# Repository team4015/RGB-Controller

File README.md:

# RGB Controller
Hardware and firmware for controlling LED RGB strips on FRC robots.

## Protocol

The RGB Controller circuit board contains a PIC16F690 microcontroller that sets the RGB colour using PWM signals.  The PIC runs the C firmware found in the `firmware` folder.  The RoboRIO can talk to the PIC using the following specific protocol:

By default, the PIC waits for the byte `0xFF` on its RX line.  Any other bytes will be discarded.  Once the PIC receives the `0xFF` header byte, it will receive three more bytes from the RX line.  These three bytes are used as the RGB brightness values.  Therefore, so set the RGB colour, the RoboRIO must send a total of 4 bytes:

```python
header = 0xFF

# RGB values must be between 0 and 255
red = 128
green = 255
blue = 0

packet = [header, red, green, blue]
send(packet)
```

**NOTE:** The PIC will never respond to the RoboRIO by sending back data.  Lights are a non-critical feature of the robot so the RoboRIO should not sit around waiting for the PIC to respond.

# Serial Port

The PIC communicates with the RoboRIO over UART, using only the TX and RX lines.  You will also need to connect the GND lines between the RGB controller board and the serial port on the RoboRIO.  The baud rate must be `9600` bps (the exact baud rate is `9615` if you want to be super precise).  No parity bits are used.  The size of one byte must be 8 bits.

**IMPORTANT:**  The PIC cannot receive more than one byte at a time.  Therefore, make sure that the RoboRIO sends data one byte at a time, with a delay of 1.5 ms between each byte.  It is advised to flush the serial port TX buffer after writing each byte.  See the Python script `rgb.py` under `firmware` for an example.

# Python Test Scripts

There are two Python test scripts: `rgb.py` and `rainbow.py`.  `rgb.py` is used to set a specific RGB colour once.  `rainbow.py` will run through the colour spectrum.

First install `pyserial`:
```
pip3 install pyserial
```

To run `rgb.py`:
```
python3 rgb.py <red> <green> <blue>
```
`red`, `green`, and `blue` must be values from `0` to `255`.

To run `rainbow.py`:
```
python3 rainbow.py
```

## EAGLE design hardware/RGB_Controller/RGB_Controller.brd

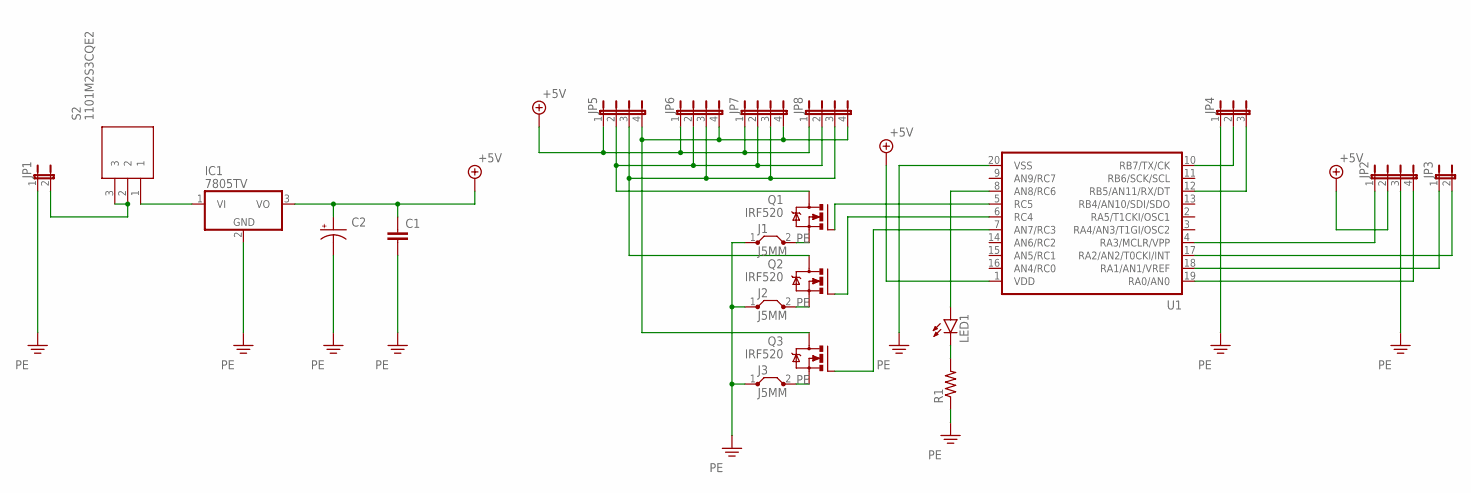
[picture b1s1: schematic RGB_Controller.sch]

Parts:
C1: C-EU025-024X044; C025-024X044
C2: CPOL-USE3.5-10; E3,5-10
IC1: 7805TV; TO220V
J1, J2, J3: J5MM; 05
JP1, JP3: JP1E; JP1
JP2, JP5, JP6, JP7, JP8: JP4E; JP4
JP4: JP2E; JP2
LED1: LED5MM
Q1, Q2, Q3: IRF520; TO220BV
R1: R-US_0207/10; 0207/10
S2: 1101M2S3CQE2; 1000-SERIES(SPDT)
U1: PIC16F6XX; DIL20

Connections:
+5V: C1.1, C2.+, IC1.3 (VO), JP2.2, JP5.1, JP6.1, JP7.1, JP8.1, U1.1 (VDD)
unnamed: JP1.2, S2.2, S2.3
unnamed: JP2.1, U1.4 (RA3/MCLR/VPP)
unnamed: LED1.K (C), R1.2
unnamed: JP2.4, U1.19 (RA0/AN0)
unnamed: JP3.1, U1.18 (RA1/AN1/VREF)
unnamed: JP3.2, U1.17 (RA2/AN2/T0CKI/INT)
unnamed: JP4.2, U1.10 (RB7/TX/CK)
unnamed: JP4.3, U1.12 (RB5/AN11/RX/DT)
unnamed: Q1.G, U1.5 (RC5)
unnamed: Q2.G, U1.6 (RC4)
unnamed: Q3.G, U1.7 (AN7/RC3)
unnamed: JP5.2, JP6.2, JP7.2, JP8.2, Q1.D
unnamed: JP5.3, JP6.3, JP7.3, JP8.3, Q2.D
unnamed: JP5.4, JP6.4, JP7.4, JP8.4, Q3.D
unnamed: LED1.A, U1.8 (AN8/RC6)
unnamed: IC1.1 (VI), S2.1
PE: C1.2, C2.-, IC1.2 (GND), J1.1, J1.2, J2.1, J2.2, J3.1, J3.2, JP1.1, JP2.3, JP4.1, Q1.S, Q2.S, Q3.S, R1.1, U1.20 (VSS)

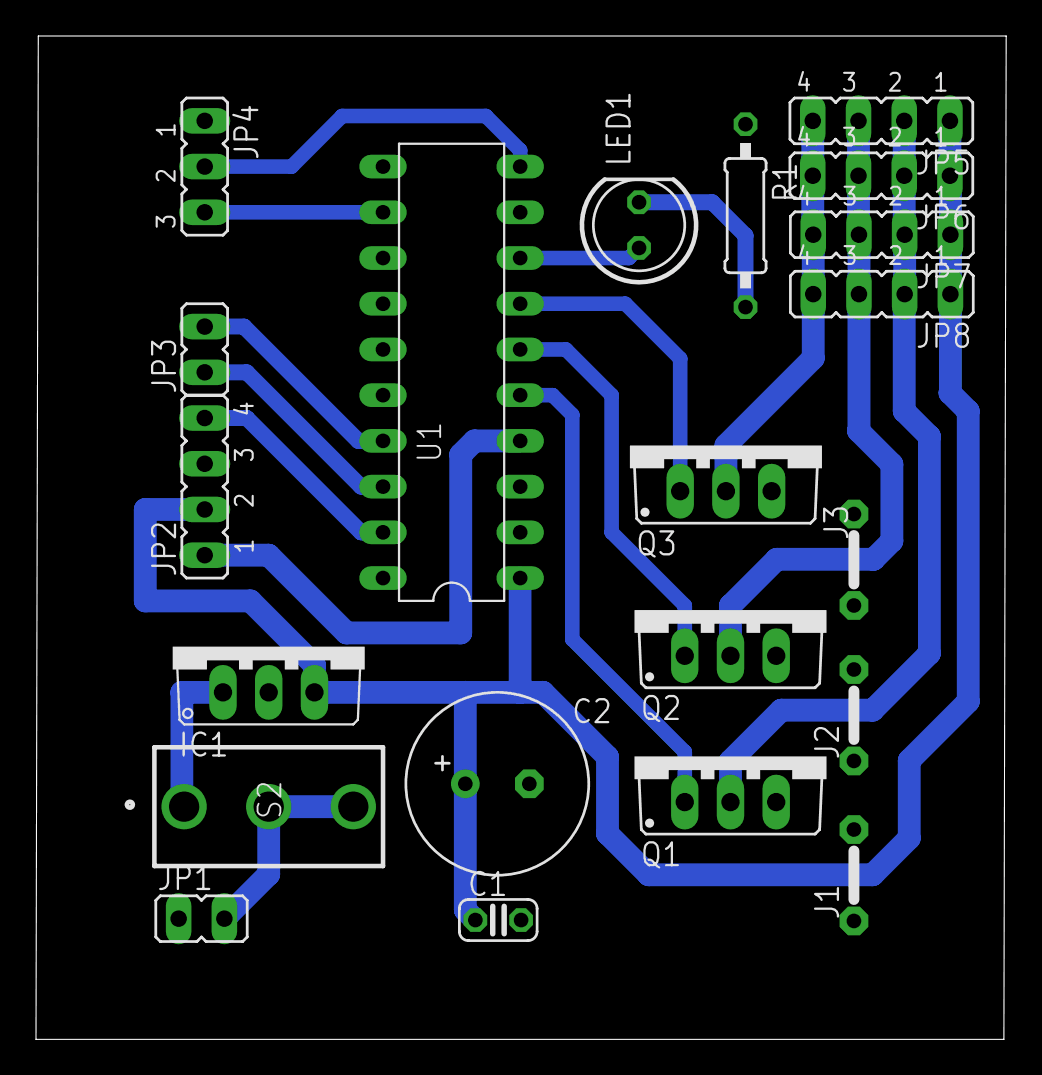
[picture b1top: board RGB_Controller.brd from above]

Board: 2 copper layers, 53.9 x 55.7 mm, 21 parts (0 on the bottom side), 18 nets.

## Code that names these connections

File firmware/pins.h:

#ifndef PINS_H
#define PINS_H

// STATUS LED //

#define LED        RC6
#define LED_TRIS   TRISC6

// RGB LEDS //

#define RED     RC4
#define GREEN   RC5
#define BLUE    RC3

#define RED_TRIS     TRISC4
#define GREEN_TRIS   TRISC5
#define BLUE_TRIS    TRISC3

#endif /* PINS_H */

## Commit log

2022-02-26 Initialization code
2022-02-26 Add Makefile
2022-03-06 Gitignore artifacts
2022-03-06 1200 baud
2022-03-07 9600 baud
2022-03-07 LED code
2022-03-07 PWM attempt with Timer0
2022-03-07 Use Timer2 instead because it's faster
2022-03-07 20 kHz PWM refresh rate with useable UART
2022-03-07 API for setting RGB PWM colours
2022-03-07 Go back to 10 kHz interrupt to avoid UART starvation
2022-03-07 Go back to 20 kHz due to flickering
2022-03-07 Settle on 13.3 kHz
2022-03-07 Clean up UART
2022-03-07 Receive RGB values over UART
2022-03-07 Reset counters when setting brightness
2022-03-08 Finalize protocol for setting colour
2022-03-08 Python test script
2022-03-14 README
2022-03-14 Notes on exact baud rate
2022-03-17 Completed Hardware Files
    - Completed schematic and board design
2022-03-18 Fixed Colour Inconsistency
    - Changed flushOutput() from serial to flush() function
2022-03-19 Don't reset counters when setting new brightness
2022-03-21 Added Sip Pins
2022-03-24 10ms TX delay README
2022-03-27 Fix typo in README
2022-04-02 Firmware Updates
    - Updated firmware
    - Added a demo script to run through all colours
2022-04-02 gitignore update
2022-04-03 Update TX delay comments
2022-04-03 Ignore __pycache__
2022-04-03 FIFO implementation
2022-04-04 Attempt to use ISR for UART RX
2022-04-04 Bump to 8 MHz and back off on interrupt frequency
2022-04-04 Swap green and blue pins
2022-04-04 Clean up test scripts
